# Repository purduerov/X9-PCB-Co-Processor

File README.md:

# X9-PCB-Shield

The shield over the Raspberry Pi

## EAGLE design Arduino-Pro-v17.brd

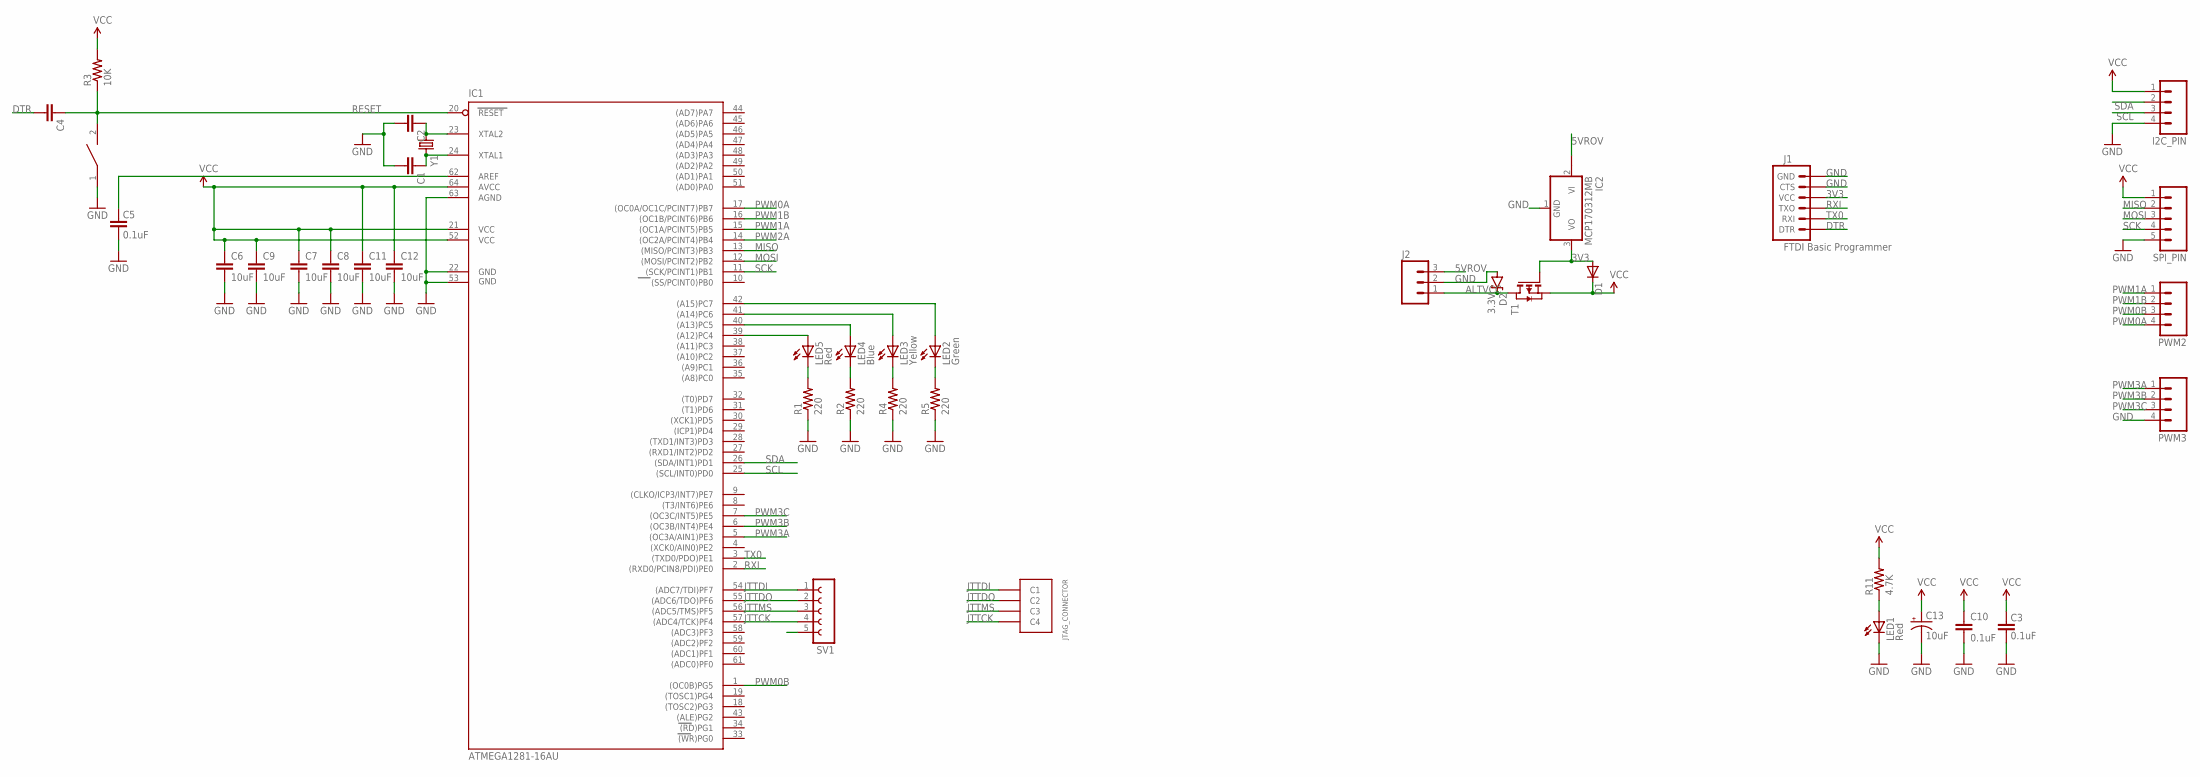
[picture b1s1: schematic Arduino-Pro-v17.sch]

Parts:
C1, C2, C4: CAP0603-CAP; 0603-CAP
C3, C5, C10: 0.1uF; 0402-CAP
C6, C7, C8, C9, C11, C12: 10uF; 0603-CAP
C13: 10uF; EIA3216
D1: DIODE-DO-214AC; DO-214AC
D2: 3.3V; SOD-323
I2C_PIN: M04PTH; 1X04
IC1: ATMEGA1281-16AU; TQFP64
IC2: MCP170312MB; SOT89
J1: FTDI Basic Programmer; 1X06
J2: M03PTH; 1X03
JTAG_CONNECTOR: MICRO-FIT-4-SMD-PART; MICRO-FIT-4-SMD
LED1, LED5: Red; LED-0603
LED2: Green; LED-0603
LED3: Yellow; LED-0603
LED4: Blue; LED-0603
PWM2, PWM3: M04PTH; 1X04
R1, R2, R4, R5: 220; 0402-RES
R3: 10K; 0603-RES
R11: 4.7K; 0402-RES
SPI_PIN: M05PTH; 1X05
SV1: FE05-1
T1: FDN340P; SOT-23
U$1: SWITCH; SW_2512
Y1: CRYSTALHC49US; HC49US

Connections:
3V3: D1.A, IC2.3 (VO), J1.4 (VCC), T1.3 (G)
5VROV: IC2.2@1 (VI1), J2.3
ALTVCC: D2.C, J2.1, T1.1 (D)
DTR: C4.2, J1.1 (DTR)
GND: C1.2, C2.2, C3.1, C5.1, C6.2, C7.2, C8.2, C9.2, C10.2, C11.2, C12.2, C13.C (-), D2.A, I2C_PIN.4, IC1.22 (GND), IC1.53 (GND1), IC1.63 (AGND), IC2.1 (GND), J1.5 (CTS), J1.6 (GND), J2.2, LED1.C, PWM3.4, R1.1, R2.1, R4.1, R5.1, SPI_PIN.5, SV1.5, U$1.1
JTTCK: IC1.57 ((ADC4/TCK)PF4), JTAG_CONNECTOR.C4, SV1.4
JTTDI: IC1.54 ((ADC7/TDI)PF7), JTAG_CONNECTOR.C1, SV1.1
JTTDO: IC1.55 ((ADC6/TDO)PF6), JTAG_CONNECTOR.C2, SV1.2
JTTMS: IC1.56 ((ADC5/TMS)PF5), JTAG_CONNECTOR.C3, SV1.3
MISO: IC1.13 ((MISO/PCINT3)PB3), SPI_PIN.2
MOSI: IC1.12 ((MOSI/PCINT2)PB2), SPI_PIN.3
unnamed: C1.1, IC1.24 (XTAL1), Y1.2
unnamed: C2.1, IC1.23 (XTAL2), Y1.1
unnamed: IC1.39 ((A12)PC4), LED5.A
unnamed: C5.2, IC1.62 (AREF)
unnamed: IC1.40 ((A13)PC5), LED4.A
unnamed: IC1.41 ((A14)PC6), LED3.A
unnamed: IC1.42 ((A15)PC7), LED2.A
unnamed: LED5.C, R1.2
unnamed: LED4.C, R2.2
unnamed: LED3.C, R4.2
unnamed: LED2.C, R5.2
unnamed: LED1.A, R11.1
PWM0A: IC1.17 ((OC0A/OC1C/PCINT7)PB7), PWM2.4
PWM0B: IC1.1 ((OC0B)PG5), PWM2.3
PWM1A: IC1.15 ((OC1A/PCINT5)PB5), PWM2.1
PWM1B: IC1.16 ((OC1B/PCINT6)PB6), PWM2.2
PWM2A: IC1.14 ((OC2A/PCINT4)PB4)
PWM3A: IC1.5 ((OC3A/AIN1)PE3), PWM3.1
PWM3B: IC1.6 ((OC3B/INT4)PE4), PWM3.2
PWM3C: IC1.7 ((OC3C/INT5)PE5), PWM3.3
RESET: C4.1, IC1.20 (RESET), R3.1, U$1.2
RXI: IC1.2 ((RXD0/PCIN8/PDI)PE0), J1.3 (TXO)
SCK: IC1.11 ((SCK/PCINT1)PB1), SPI_PIN.4
SCL: I2C_PIN.3, IC1.25 ((SCL/INT0)PD0)
SDA: I2C_PIN.2, IC1.26 ((SDA/INT1)PD1)
TX0: IC1.3 ((TXD0/PDO)PE1), J1.2 (RXI)
VCC: C3.2, C6.1, C7.1, C8.1, C9.1, C10.1, C11.1, C12.1, C13.A (+), D1.C, I2C_PIN.1, IC1.21 (VCC), IC1.52 (VCC1), IC1.64 (AVCC), R3.2, R11.2, SPI_PIN.1, T1.2 (S)

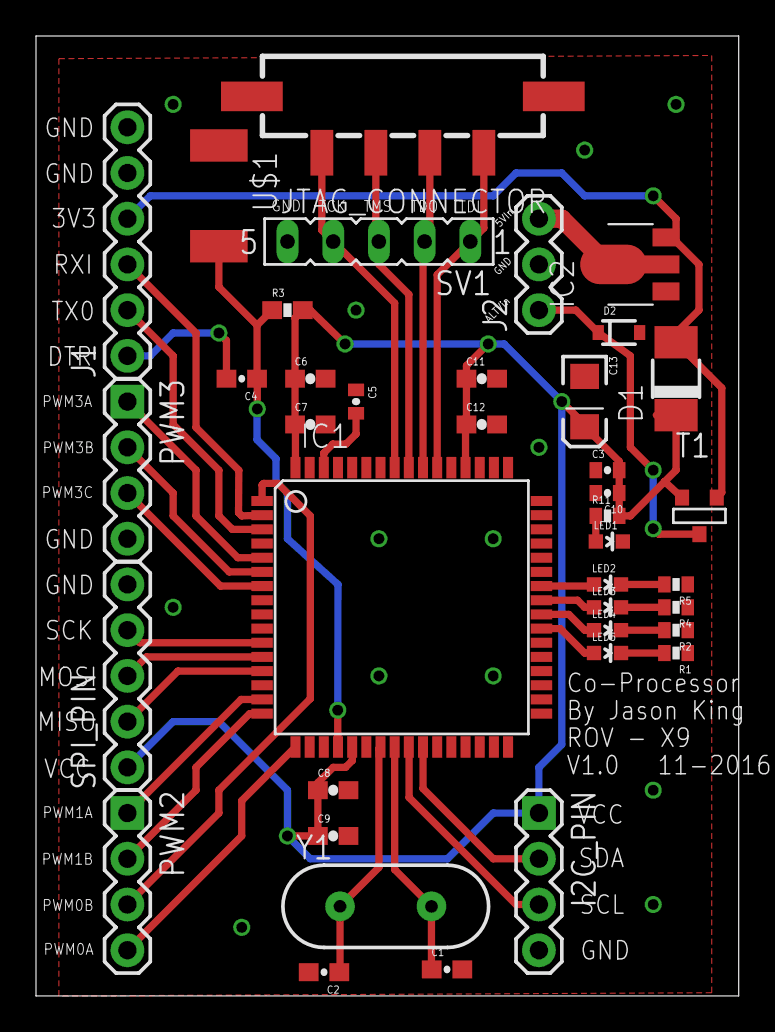
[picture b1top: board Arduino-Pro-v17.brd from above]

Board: 2 copper layers, 39.0 x 53.3 mm, 39 parts (0 on the bottom side), 37 nets.

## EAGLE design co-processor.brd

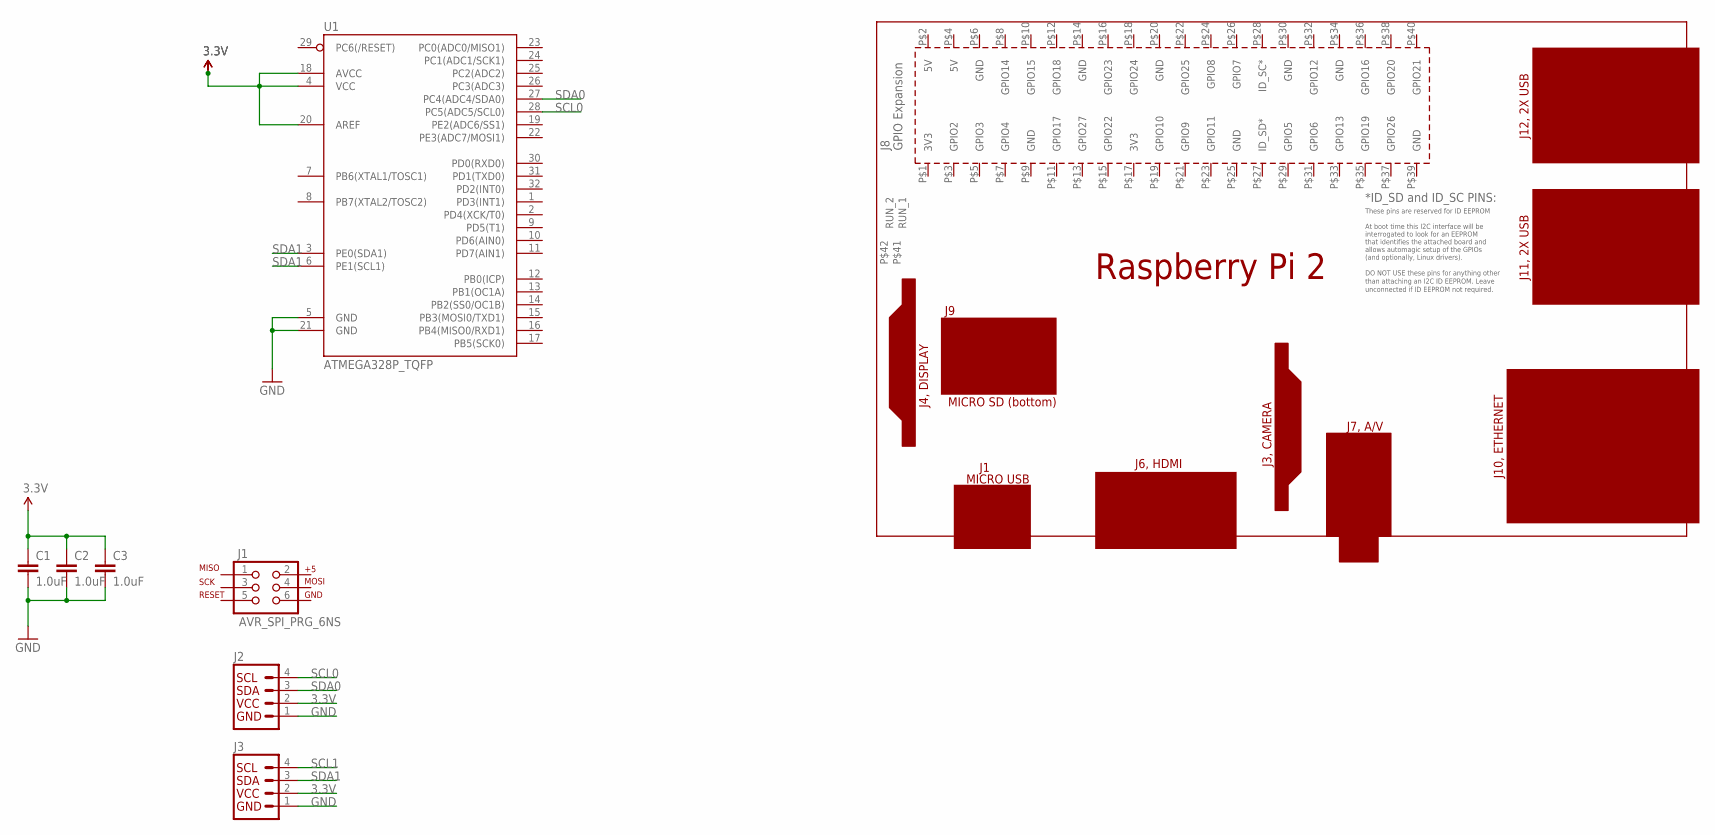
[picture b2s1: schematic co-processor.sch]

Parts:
C1, C2, C3: 1.0uF; 0603-CAP
J1: AVR_SPI_PRG_6NS; 2X3-NS
J2, J3: I2C_STANDARD; 1X04
PCB1: RPI2
U1: ATMEGA328P_TQFP; TQFP32-08

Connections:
3.3V: C1.1, C2.1, C3.1, J2.2, J3.2, U1.4 (VCC), U1.18 (AVCC), U1.20 (AREF)
GND: C1.2, C2.2, C3.2, J2.1, J3.1, U1.5 (GND), U1.21 (GND)
SCL0: J2.4, U1.28 (PC5(ADC5/SCL0))
SCL1: J3.4
SDA0: J2.3, U1.27 (PC4(ADC4/SDA0))
SDA1: J3.3, U1.3 (PE0(SDA1)), U1.6 (PE1(SCL1))

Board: 2 copper layers, 8 parts (0 on the bottom side), 5 nets, no tracks yet.

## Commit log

2016-09-19 initial board/scheatic layout
2016-10-01 changing the board files
2016-10-04 Added the _real_ files for the board
2016-10-04 Added BSS138 Link to components
2016-10-04 Added 16MHz oscillator Link to components
2016-10-04 Added digikey links
2016-10-05 working on schematic
2016-10-11 Modified power inputs and added a todo list
2016-10-12 Added JTAG pins and smaller pushbutton
2016-10-15 Added FTDI 3.3V programmer
2016-10-15 Added 3.3V linear regulator, delete logic level shifters
2016-10-15 Added a pin out for alternate 3.3V power supply
2016-10-15 Started ordering the layout of the board
2016-10-22 continued working on board layout, added ground plan polygon
2016-10-22 Added extra pinouts for JTAG, continued with layout
2016-10-25 Routing
2016-10-25 BC macz sukz
2016-10-25 Almost finished wiring
2016-10-25 Removed RPI board
2016-10-26 Finished routing
2016-10-26 Added ground plan to bottom of board
2016-10-26 Fixed stray route under atmel chip
2016-10-29 Fixed some things with the board layout
2016-10-29 Complete final changes
2016-11-01 Finished all routing, added pinouts for silkscreening on top of the board
2016-11-02 Ran cam job
2016-11-02 OutputJob
2018-09-13 blah

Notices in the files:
parts and their libraries:
SparkFun-Passives: Licensing: Creative Commons ShareAlike 4.0 International - https://creativecommons.org/licenses/by-sa/4.0
